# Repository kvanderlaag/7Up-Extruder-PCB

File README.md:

# 7-Up Amateur Extruder PCB

This is a replacement extruder/toolhead PCB for Creality Sprite/Sprite Pro Extruder PCB for Ender-3 series printers -- the Ender-3 S1, Ender-3 S1 Pro, Ender-3 S1 Plus, which all come with a Sprite direct drive extruder out of the box, or an Ender-3, Ender-3 Pro, or Ender-3 V2 that you've retrofitted with the Creality Sprite or Sprite Pro extruder kit.

While fumbling around behind my toolhead with a wrench to adjust the eccentric nut spacer on the X-axis, I managed to ram the wrench into the extruder connector, tearing it off the PCB and taking the solder pads and an appreciable amount of the traces connected to it with it. Naturally, I did this at the worst possible time, when I was printing parts necessary to get my _other_ printer working.

Of note: If you e-mail sales@creality3dofficial.com and request a replacement for this part, they can sell you one! It cost $15 USD shipped. However, while I was waiting to hear back from them, I looked at this PCB and thought, "hell, I could just make one of these."

The connectors on the Creality PCB are: 
- a 2.0mm-pitch, 24-position IDC header, right angle, with locking tabs and eject levers -- they need to be long enough to reach the top of the IDC connector -- for the flat flexible ribbon cable that connects to the printer; ryanpie86 has correctly pointed out that [this connector](https://www.lcsc.com/product-detail/IDC-Connectors_Ckmtw-Shenzhen-Cankemeng-B-3102R24P-A000_C383593.html) on LCSC is a perfect fit, but watch out for LCSC's shipping. It's helpful if you can place an order for a lot of crap together, and you will pay customs fees on it.
- three JST ZH (1.5mm pitch) surface-mount connectors, 2-position, for the thermistor, hotend fan, and part cooling fan
- one JST ZH (1.5mm pitch) surface-mount connector, 4-position, for the extruder motor
- one JST ZH (1.5mm pitch) surface-mount connector, 5-position, for the (optional) CRtouch/BLtouch automatic bed levelling sensor
- one JST XH (2.5mm pitch) through-hole connector, 2-position, for the heater cartridge

I don't know if you've ever soldered these ZH bastards surface-mount before, but they are absolutely hateful little things, and I refuse to do it. ZH is the smallest JST connector size you can get in through-hole flavour, so for this board, I've replaced _all_ of the surface-mount connectors with through-hole variants. I feel like this actually makes this PCB more repairable than the original, and less prone to the thing that destroyed mine in the first place.

The flat flexible cable connector is slightly more problematic. [This](https://www.digikey.ca/en/products/detail/cnc-tech/3110-24-002-13-00/3882488) connector from CnC Tech is exactly what you want -- but it is obsolete and, as far as I can tell, impossible to obtain. Creality are clearly using a connector _like_ this one in the production PCBs, but I haven't been able to find a source for it. If you do, let me know and I'll update the project and this document to point at it. For the time being, I've just carefully desoldered mine from the board and reused it. If you were desperate, you could use a regular shrouded 24-position, 2.0mm pitch, right-angle pin header, but since this part is in motion and dragging the cable around with it, this seems like it probably leads to sadness.

JST connectors are easier to come by, but at the time of this writing (2022-08-25) are spotty at best for stock, with a long lead time. You want the JST [S2B-ZR-3.4(LF)(SN)](https://www.digikey.ca/en/products/detail/jst-sales-america-inc/s2b-zr-3-4-lf-sn/4806278) for the 2-position ZH, [S4B-ZR-3.4(LF)(SN)](https://www.digikey.ca/en/products/detail/jst-sales-america-inc/s4b-zr-3-4-lf-sn/7802286) for the 4-position ZH, [S5B-ZR-3.4(LF)(SN)](https://www.digikey.ca/en/products/detail/jst-sales-america-inc/s5b-zr-3-4-lf-sn/9972250) for the 5-position ZH, and the [S2B-XH-A(LF)(SN)](https://www.digikey.ca/en/products/detail/jst-sales-america-inc/S2B-XH-A-LF-SN/1651055) for the 2-position XH for the heater.

Annoyingly, Chinese replacements available on Alibaba/AliExpress _will_ fit with some massaging, but they are listed at 2.54mm pitch rather than the 2.5mm pitch of "genuine" JSTs. I've designed the board with the JSTs in mind, but there is a distinct probability that the heater cartridge on the Sprite is actually 2.54mm pitch. Again, it should both fit and work whichever one you choose to use, it might just be a little tight on the board if you're using a Chinese XH-style connector, and a little tight fitting the cable into the connector if you're using a genuine JST. The worst of both worlds, really.

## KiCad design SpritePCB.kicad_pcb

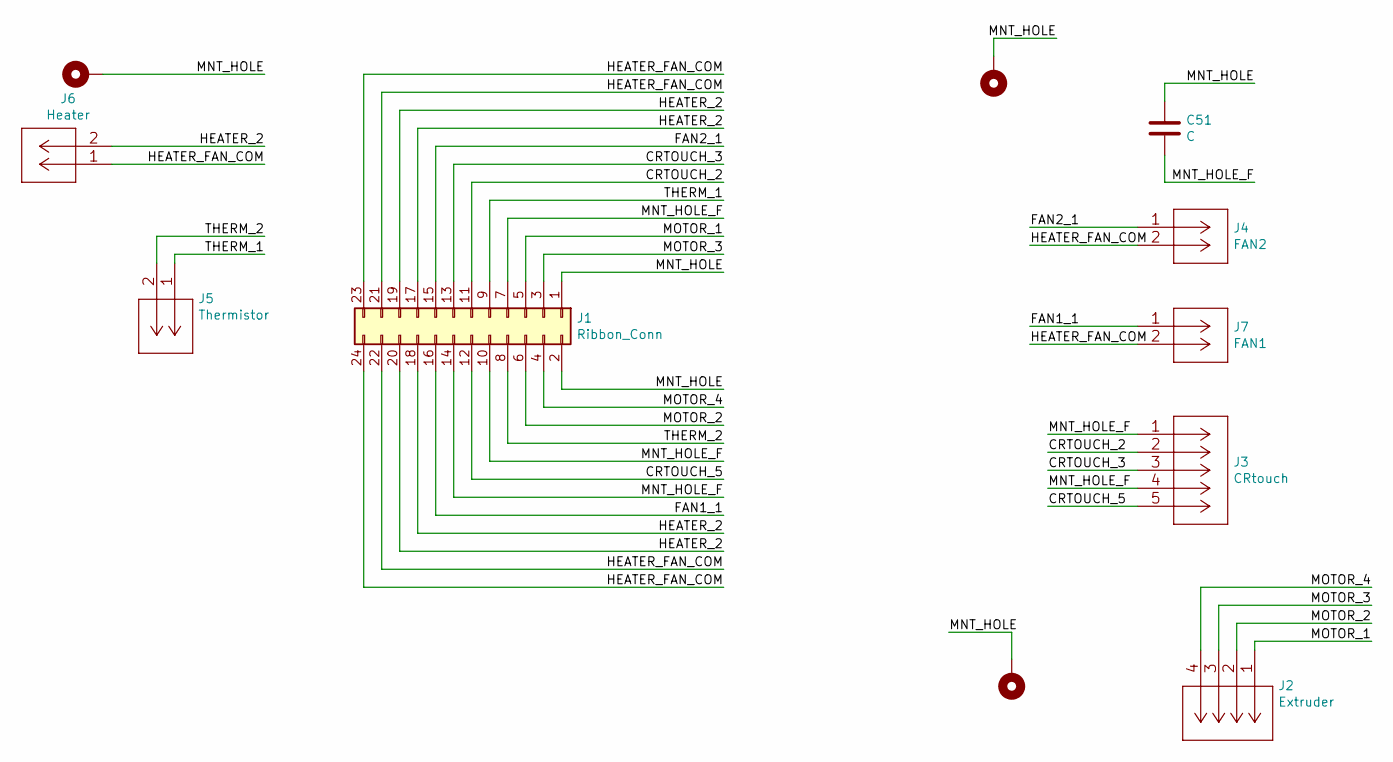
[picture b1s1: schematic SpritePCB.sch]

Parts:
C51: C; C_1210_3225Metric_Pad1.33x2.70mm_HandSolder
H1, H2: MountingHole_Pad; MountingHole_2.2mm_M2_DIN965_Pad
H3: MountingHole_Pad; MountingHole_3.2mm_M3_DIN965_Pad
J1: Ribbon_Conn; PinHeader_2x12_P2.00mm_Vertical
J2: Extruder; S4B-ZRLFSN
J3: CRtouch; S5B-ZRLFSN
J4: FAN2; S2B-ZRLFSN
J5: Thermistor; S2B-ZRLFSN
J6: Heater; S2B-XH-A-1LFSN
J7: FAN1; S2B-ZRLFSN

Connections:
/CRTOUCH_2: J1.11, J3.2
/CRTOUCH_3: J1.13, J3.3
/CRTOUCH_5: J1.12, J3.5
/FAN1_1: J1.16, J7.1
/FAN2_1: J1.15, J4.1
/HEATER_2: J1.17, J1.18, J1.19, J1.20, J6.2
/HEATER_FAN_COM: J1.21, J1.22, J1.23, J1.24, J4.2, J6.1, J7.2
/MNT_HOLE: C51.1, H1.1, H2.1, H3.1, J1.1, J1.2
/MNT_HOLE_F: C51.2, J1.7, J1.10, J1.14, J3.1, J3.4
/MOTOR_1: J1.5, J2.1
/MOTOR_2: J1.6, J2.2
/MOTOR_3: J1.3, J2.3
/MOTOR_4: J1.4, J2.4
/THERM_1: J1.9, J5.1
/THERM_2: J1.8, J5.2

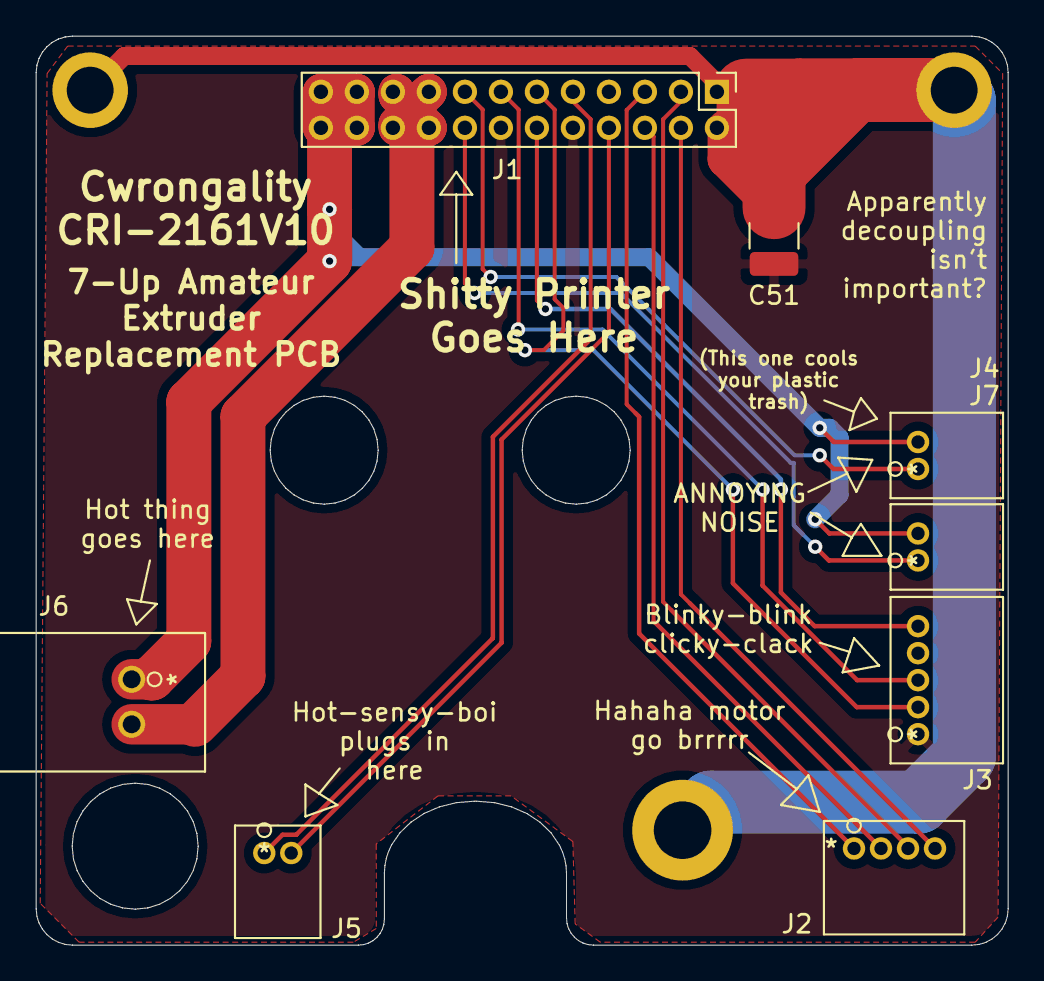
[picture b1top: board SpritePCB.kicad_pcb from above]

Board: 2 copper layers, 54.0 x 50.5 mm, 11 parts (0 on the bottom side), 15 nets.

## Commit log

2022-08-25 Initialize repository with project files
2022-09-04 Corrected misaligned drills
    Corrected misaligned motor mount hole (originally slightly too high and too far left); shifted FFC connector left slightly to align better with the cable bracket; widened cutout for POM adjuster slig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
    After receiving the first batch of boards, I noticed that I'd done math wrong on the motor mounting hole positions. (Did the math based on the edge, not the centre, because I'm stupid. I also made so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
    One thing to note: The connectors that were prev
2023-01-19 Fix issue #1: overlapping tracks/signals introduced in commit 18d3b11
    Moving the dual-row header in commit 18d3b1 resulted in misaligned traces overlapping with the new hole positions. Don't commit changes while tired, folks.
2023-05-29 Update BOM with link to 2mm-pitch 24-position IDC connector
